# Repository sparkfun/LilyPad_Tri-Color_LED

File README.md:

SparkFun LilyPad RGB LED
========================================

[*SparkFun LilyPad RGB LED (DEV-13735)*](https://www.sparkfun.com/products/13735)

Use the LilyPad RGB LED board as a simple indicator, or by pulsing the red, green, and blue channels, you can create any color. 
This is a common cathode design - to turn on a channel you simply need to connect each R/G/B pins to a power source in order to illuminate that channel.

_Note: The original product name was called "LilyPad Tri-Color LED." V2.0 was renamed as the "LilyPad RGB LED."_

Repository Contents
-------------------
* **/Firmware** - Arduino example code 
* **/Hardware** - All Eagle design files (.brd, .sch)

Documentation
--------------
* **[SparkFun Fritzing repo](https://github.com/sparkfun/Fritzing_Parts)** - Fritzing diagrams for SparkFun products.
* **[Hookup Guide](https://learn.sparkfun.com/tutorials/lilypad-rgb-led-hookup-guide)** - Basic hookup guide for the LilyPad RGB LED.

Version History
---------------
* [v2.0](https://github.com/sparkfun/LilyPad_Tri-Color_LED/tree/v_2.0) - v2.0, common cathode
* [v1.6](https://github.com/sparkfun/LilyPad_Tri-Color_LED/tree/v_1.6) - Initial Release, common anode

License Information
-------------------
The hardware is released under [Creative Commons ShareAlike 4.0 International](https://creativecommons.org/licenses/by-sa/4.0/).

A portion of this sale is given back to Dr. Leah Buechley for continued development and education of e-textiles.

Distributed as-is; no warranty is given.

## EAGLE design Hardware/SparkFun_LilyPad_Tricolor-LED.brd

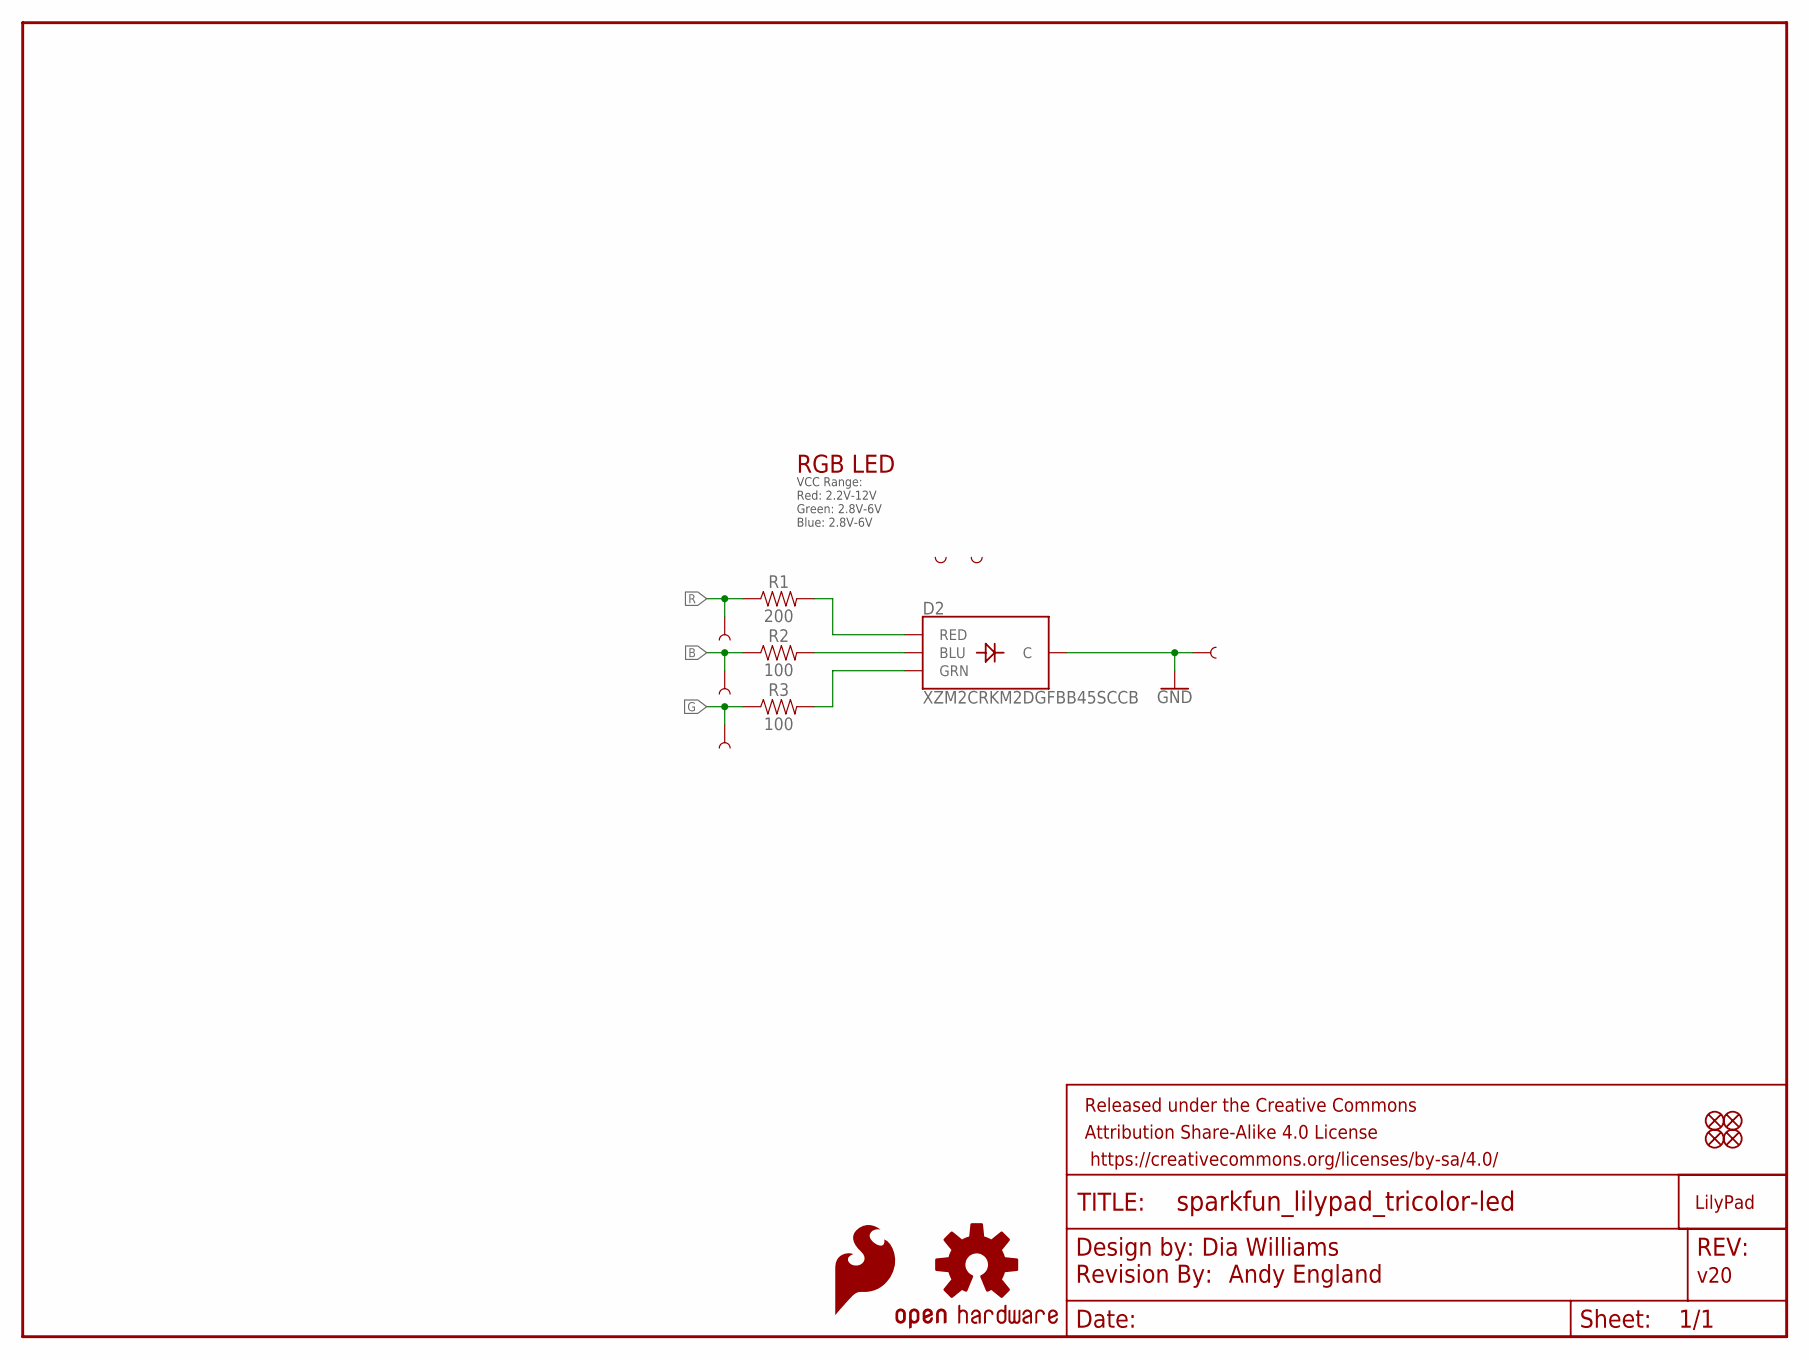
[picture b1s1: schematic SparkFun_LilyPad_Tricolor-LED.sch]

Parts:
D2: XZM2CRKM2DGFBB45SCCB; PLCC4SMDLED
FD1, FD2, FD3, FD4: FIDUCIAL1X2; FIDUCIAL-1X2
FRAME1: FRAME-LETTER; CREATIVE_COMMONS
LOGO1: REVISION
LOGO2: OSHW-LOGOS; OSHW-LOGO-S
LOGO3: SFE_LOGO_FLAME.1_INCH; SFE_LOGO_FLAME_.1
R1: 200; 0603
R2, R3: 100; 0603
U$1: LOGO-LPLP; LOGO-LILYPAD
U$2, U$3: SEWTAP-NOHOLE2; PETAL-NOHOLE-2SIDE
U$7, U$8, U$9, U$10: SEWTAP6; PETAL-SMALL-2SIDE

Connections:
B: R2.1, U$9.1
BLU: D2.3 (BLU), R2.2
G: R3.1, U$8.1
GND: D2.4 (C), U$10.1
GRN: D2.2 (GRN), R3.2
R: R1.1, U$7.1
RED: D2.1 (RED), R1.2

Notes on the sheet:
v20
Andy England
RGB LED
Dia Williams
VCC Range: Red: 2.2V-12V Green: 2.8V-6V Blue: 2.8V-6V

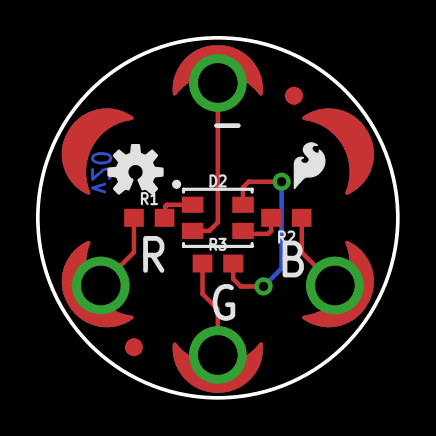
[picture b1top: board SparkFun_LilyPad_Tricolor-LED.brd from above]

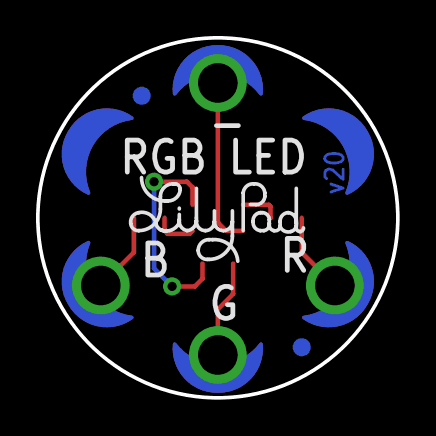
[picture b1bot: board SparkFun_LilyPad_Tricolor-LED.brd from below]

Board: 2 copper layers, 20.0 x 20.0 mm, 20 parts (3 on the bottom side), 7 nets.

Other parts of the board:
U$4: ORDERING_INSTRUCTIONS

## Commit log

2015-01-29 Initial hardware commit
2015-01-29 Fixing image url in README
2018-04-20 Rename BasicColorMixing/BasicColorMixing.ino to Firmware/BasicColorMixing/BasicColorMixing.ino
2018-10-08 revising to common cathode LED
2018-10-09 revising to common cathode
2018-10-10 post design review changes
2018-10-18 updating
2018-10-18 post review
2019-07-08 Code for Common Cathode RGB LED
    - Add new code for a Common Cathode RGB LED
    - Adjust example code file names to distinguish between common anode and common cathode

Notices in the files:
parts and their libraries:
SparkFun-LED: Licensing: Creative Commons ShareAlike 4.0 International - https://creativecommons.org/licenses/by-sa/4.0
SparkFun-Aesthetics: Released under the Creative Commons Attribution Share-Alike 4.0 License
SparkFun-Aesthetics: Released under the Creative Commons
